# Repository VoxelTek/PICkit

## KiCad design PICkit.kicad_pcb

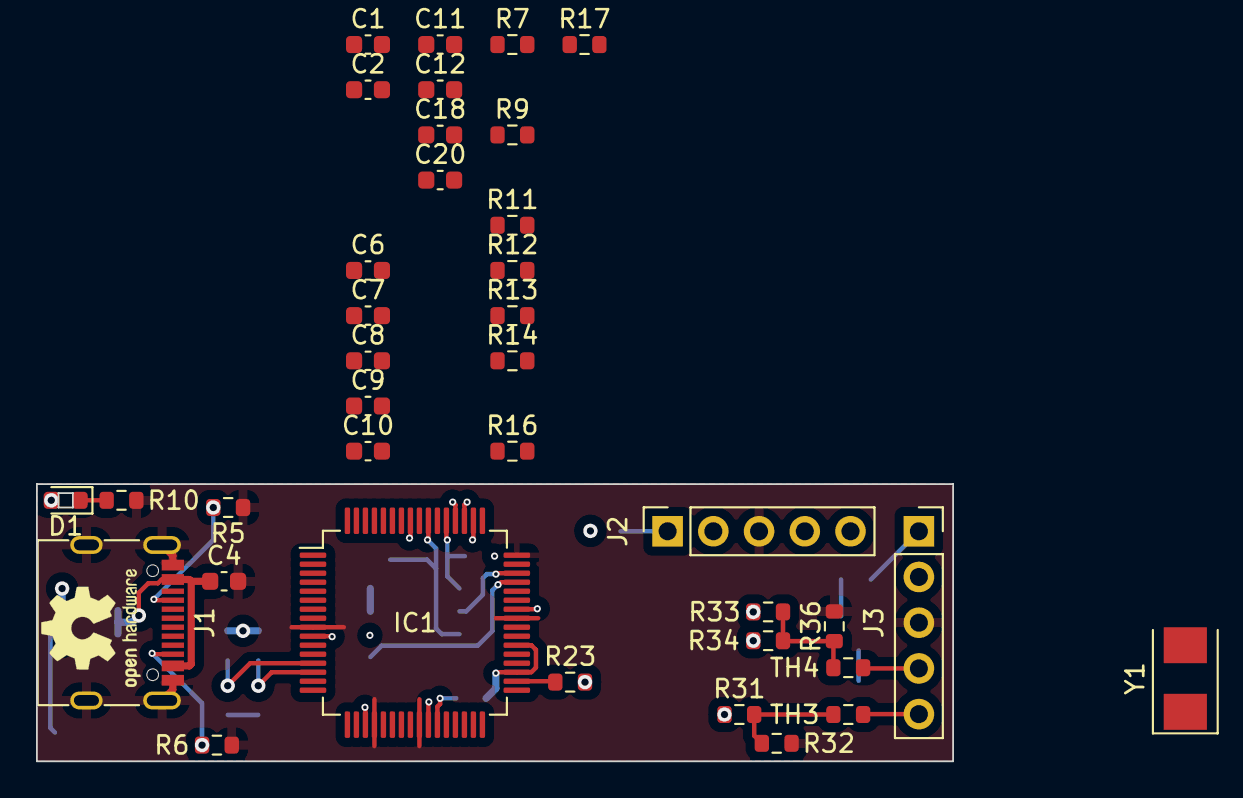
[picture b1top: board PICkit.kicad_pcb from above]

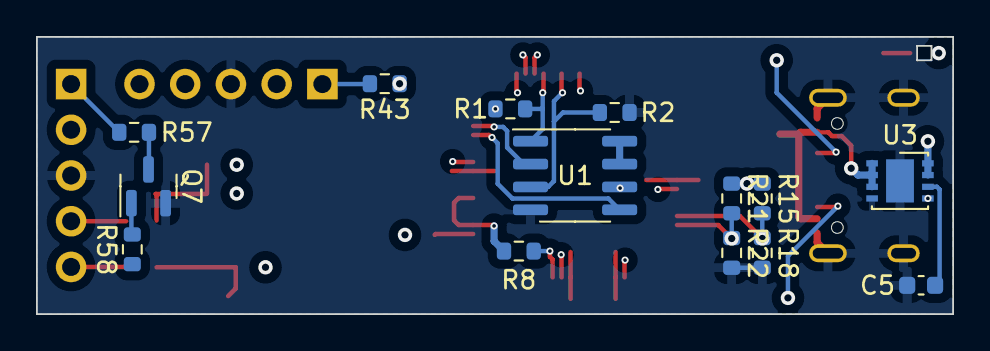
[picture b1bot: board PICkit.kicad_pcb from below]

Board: 4 copper layers, 50.9 x 15.4 mm, 51 parts (14 on the bottom side), 41 nets.

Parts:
C1: 10uF; C_0603_1608Metric
C2, C11: 1uF; C_0603_1608Metric
C4, C7: 2.2uF; C_0603_1608Metric
C5, C6, C12, C18, C20: 0.1uF; C_0603_1608Metric
C8: 10nF; C_0603_1608Metric
C9, C10: 22pF; C_0603_1608Metric
D1: GREEN; LED_0603_1608Metric
IC1: PIC24FJ256GB106-I_PT; TQFP-64_10x10mm_P0.5mm
J1: USB_C_Receptacle_USB2.0; USB_C_Receptacle_G-Switch_GT-USB-7010ASV
J2, J3: Conn_01x05; PinSocket_1x05_P2.54mm_Vertical
Q7: MMBT3904; SOT-23
R1, R15, R43, R58: 10k; R_0603_1608Metric
R2, R11: 1k; R_0603_1608Metric
R5, R6: 5.1k; R_0603_1608Metric
R7, R10, R31, R33, R34: 330; R_0603_1608Metric
R8, R14, R16, R17: 200k; R_0603_1608Metric
R9: 2.2k; R_0603_1608Metric
R12: 3.16k; R_0603_1608Metric
R13, R57: 100k; R_0603_1608Metric
R18, R22: 2.21k; R_0603_1608Metric
R21: 3.92k; R_0603_1608Metric
R23: 100; R_0603_1608Metric
R32, R36: 4.7k; R_0603_1608Metric
TH3, TH4: MICROSMD005F; R_0603_1608Metric
U1: 25LC256; SOIC-8_3.9x4.9mm_P1.27mm
U3: MCP1727-0802xMF; DFN-8-1EP_3x3mm_P0.65mm_EP1.55x2.4mm
Y1: 12MHz; Crystal_SMD_5032-2Pin_5.0x3.2mm

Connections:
+3.3V: C2.1, C6.1, C7.1, C8.1, C11.1, C12.1, C18.1, C20.1, D1.2 (A), IC1.10 (VDD_1), IC1.19 (AVDD), IC1.26 (VDD_2), IC1.35 (VUSB), IC1.38 (VDD_3), IC1.57 (ENVREG), J2.2, J3.2, R1.2, R8.1, R9.1, R11.1, R13.1, R15.1, R16.1, R17.1, R21.1, R43.1, U1.7 (~HOLD), U1.8 (VCC), U3.7 (Sense), U3.8 (Vout)
/VREF_2.5V: IC1.16 (PGED1/AN0/VREF+/RP0/PMA6/CN2/RB0), R11.2, R12.1
/XOSC_+: C9.1, IC1.40 (OSCO/CLKO/CN22/RC15), Y1.2
/XOSC_-: C10.1, IC1.39 (OSCI/CLKI/CN23/RC12), Y1.1
D+: IC1.37 (D+/RG2), J1.A6 (D+), J1.B6 (D+)
D-: IC1.36 (D-/RG3), J1.A7 (D-), J1.B7 (D-)
DBG_RX1: IC1.32 (SCL2/RP17/PMA8/CN18/RF5), R17.2
DBG_TX1: IC1.31 (SDA2/RP10/PMA9/CN17/RF4), R16.2
GND: C1.2, C2.2, C4.2, C5.2, C6.2, C7.2, C8.2, C9.2, C10.2, C11.2, C12.2, C18.2, C20.2, IC1.9 (VSS_1), IC1.20 (AVSS), IC1.25 (VSS_2), IC1.41 (VSS_3), IC1.47 (SOSCI/C3IND/CN1/RC13), IC1.48 (SOSCO/T1CK/C3INC/RPI37/CN0/RC14), J1.A1 (GND), J1.A12 (GND), J1.B1 (GND), J1.B12 (GND), J1.S1 (SHIELD), J2.3, J3.3, Q7.2 (E), R2.1, R5.1, R6.2, R9.2, R10.2, R12.2, R14.2, R18.2, R22.2, R32.1, R36.1, U1.4 (GND), U3.4 (GND), U3.9 (GND)
ICSP_CLK: J3.5, TH3.1
ICSP_DAT: J3.4, TH4.1
MCLR: J3.1, R57.1
MICRO_PGC: IC1.17 (PGEC2/AN6/RP6/CN24/RB6), J2.5
MICRO_PGD: IC1.18 (PGED2/AN7/RP7/RCV/CN25/RB7), J2.4
MICRO_~MCLR: J2.1, R7.2, R43.2
MISO: IC1.51 (RP22/PMBE/CN52/RD3), R33.1
MOSI: IC1.52 (RP25/PMWR/CN13/RD4), R34.1
unnamed: D1.1 (K), R10.1
unnamed: IC1.63 (PMD3/CN61/RE3), R14.1
unnamed: IC1.64 (PMD4/CN62/RE4), R13.2
unnamed: C1.1, IC1.56 (VCAP/VDDCORE)
unnamed: IC1.7 (~MCLR), R7.1
unnamed: J1.A5 (CC1), R5.2
unnamed: J1.B5 (CC2), R6.1
unnamed: Q7.1 (B), R58.2
unnamed: Q7.3 (C), R57.2
unnamed: R31.2, R32.2, TH3.2
unnamed: R33.2, R34.2, R36.2, TH4.2
unnamed: C5.1, U3.6 (Cdelay)
POWER_GOOD: IC1.27 (TCK/AN12/PMA11/CTED2/CN30/RB12), R8.2, U3.5 (PWRGD)
SCLK: IC1.50 (DPH/RP23/CN51/RD2), R31.1
UTIL_CS1: IC1.53 (RP20/PMRD/CN14/RD5), R1.1, U1.1 (~CS)
UTIL_MISO: IC1.45 (RP12/PMCS1/CN56/RD11), U1.5 (SDI)
UTIL_MOSI: IC1.46 (DMH/RP11/INT0/CN49/RD0), U1.2 (SDO)
UTIL_SCLK: IC1.42 (RTCC/DMLN/RP2/CN53/RD8), U1.6 (SCK)
UTIL_WP1: IC1.55 (C3INA/CN16/RD7), R2.2, U1.3 (~WP)
VBUS: C4.1, J1.A4 (VBUS), J1.A9 (VBUS), J1.B4 (VBUS), J1.B9 (VBUS), R23.2, U3.1 (Vin), U3.2 (Vin), U3.3 (~SHDN)
VBUS_DEVICE: IC1.34 (VBUS), R23.1
VDD_FBACK: IC1.14 (AN2/C2INB/VMIO/RP13/CN4/RB2), R21.2, R22.1
VPP_FBACK: IC1.13 (AN3/C2INA/VPIO/CN5/RB3), R15.2, R18.1
VPP_GND: IC1.2 (SCL3/PMD6/CN64/RE6), R58.1

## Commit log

2024-01-01 Starting routing from scratch
2024-01-02 more routing
2024-01-02 Begun work on mini
